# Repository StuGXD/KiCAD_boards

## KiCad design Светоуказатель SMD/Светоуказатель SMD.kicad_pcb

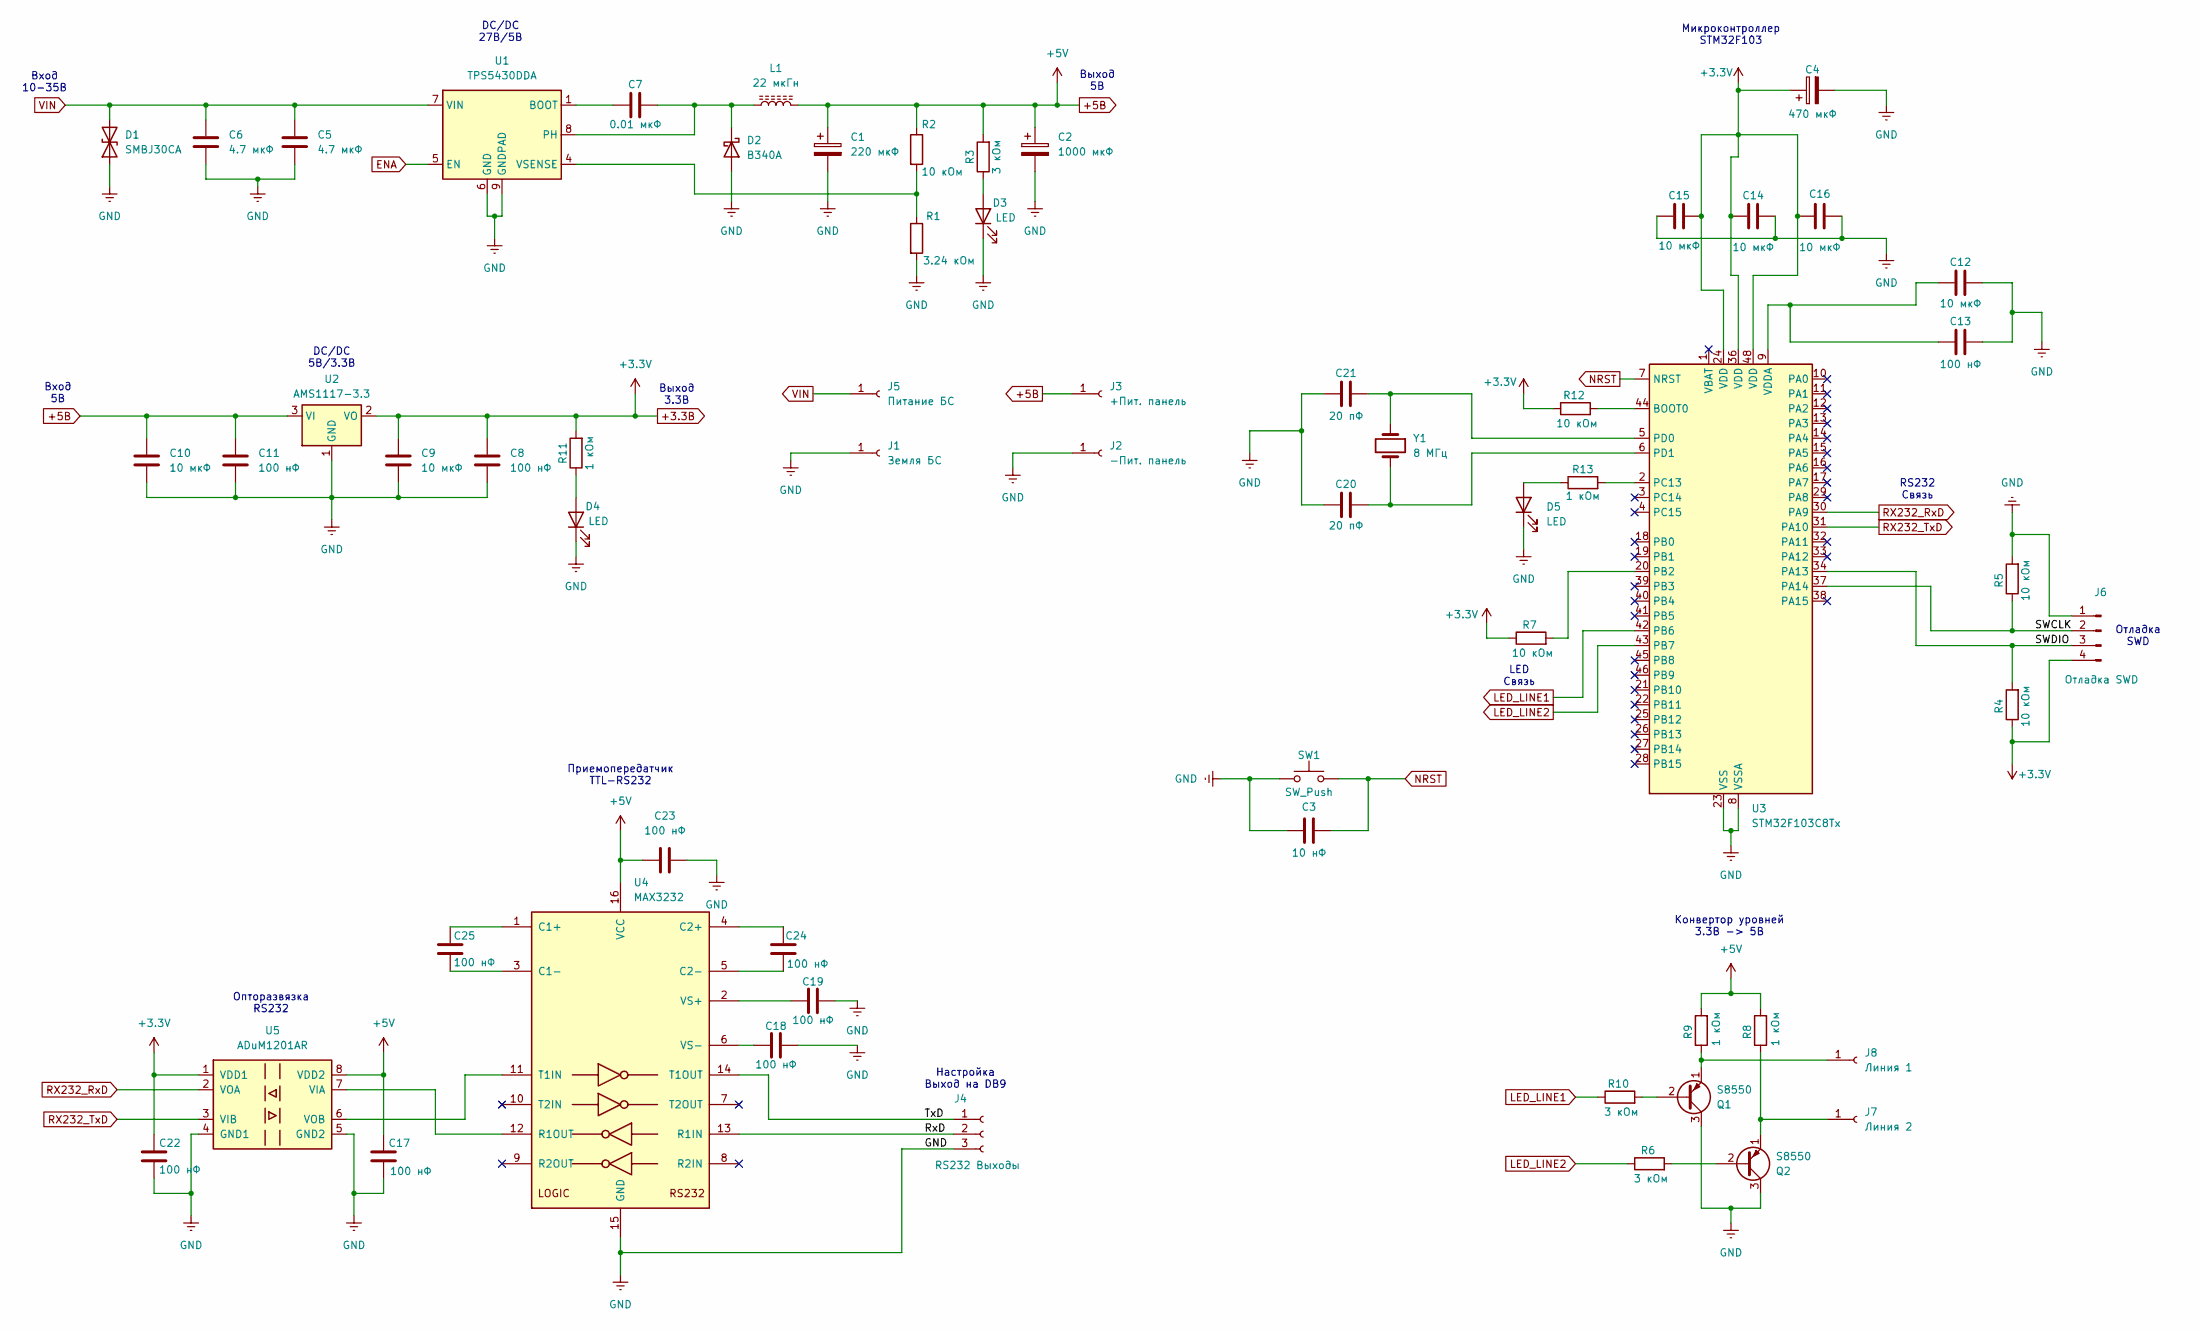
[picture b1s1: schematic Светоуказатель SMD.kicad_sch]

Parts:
C1: 220 мкФ; C_0603_1608Metric
C2: 1000 мкФ; CP_EIA-7343-43_Kemet-X_Pad2.25x2.55mm_HandSolder
C3: 10 нФ; C_0603_1608Metric
C4: 470 мкФ; CP_EIA-7343-43_Kemet-X_Pad2.25x2.55mm_HandSolder
C5, C6: 4.7 мкФ; C_0603_1608Metric
C7: 0.01 мкФ; C_0603_1608Metric
C8, C11, C13, C17, C18, C19, C22, C23, C24, C25: 100 нФ; C_0603_1608Metric
C9, C10, C12, C14, C15, C16: 10 мкФ; C_0603_1608Metric
C20, C21: 20 пФ; C_0603_1608Metric
D1: SMBJ30CA; D_SMB
D2: B340A; D_SMC
D3, D4, D5: LED; LED_0603_1608Metric
J1: Земля БС; SolderWire-2.5sqmm_1x01_D2.4mm_OD4.4mm
J2: -Пит. панель; SolderWire-2.5sqmm_1x01_D2.4mm_OD4.4mm
J3: +Пит. панель; SolderWire-2.5sqmm_1x01_D2.4mm_OD4.4mm
J4: RS232 Выходы; SolderWire-1sqmm_1x03_P7.8mm_D1.4mm_OD3.9mm
J5: Питание БС; SolderWire-2.5sqmm_1x01_D2.4mm_OD4.4mm
J6: Отладка SWD; PinHeader_1x04_P2.54mm_Vertical
J7: Линия 2; SolderWire-2.5sqmm_1x01_D2.4mm_OD4.4mm
J8: Линия 1; SolderWire-2.5sqmm_1x01_D2.4mm_OD4.4mm
L1: 22 мкГн; L_Bourns_SRR1260
Q1, Q2: S8550; SOT-23
R1: 3.24 кОм; R_0603_1608Metric
R2, R4, R5, R7, R12: 10 кОм; R_0603_1608Metric
R3, R6, R10: 3 кОм; R_0603_1608Metric
R8, R9, R11, R13: 1 кОм; R_0603_1608Metric
SW1: SW_Push; SW_SPST_CK_RS282G05A3
U1: TPS5430DDA; TI_SO-PowerPAD-8_ThermalVias
U2: AMS1117-3.3; SOT-223-3_TabPin2
U3: STM32F103C8Tx; LQFP-48_7x7mm_P0.5mm
U4: MAX3232; TSSOP-16_4.4x5mm_P0.65mm
U5: ADuM1201AR; SOIC-8_3.9x4.9mm_P1.27mm
Y1: 8 МГц; Crystal_SMD_HC49-SD

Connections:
+3.3В: C4.1, C8.1, C9.1, C14.2, C15.2, C16.1, C22.2, J6.4, R4.1, R7.1, R11.2, R12.1, U2.2 (VO), U3.24 (VDD), U3.36 (VDD), U3.48 (VDD), U5.1 (VDD1)
+5В: C1.1, C2.1, C10.1, C11.1, C17.1, C23.1, J3.1, L1.2, R2.1, R3.2, R8.2, R9.2, U2.3 (VI), U4.16 (VCC), U5.8 (VDD2)
/RxD: J4.2, U4.13 (R1IN)
/SWCLK: J6.2, R5.1, U3.37 (PA14)
/SWDIO: J6.3, R4.2, U3.34 (PA13)
/TxD: J4.1, U4.14 (T1OUT)
ENA: U1.5 (EN)
GND: C1.2, C2.2, C3.1, C4.2, C5.2, C6.2, C8.2, C9.2, C10.2, C11.2, C12.2, C13.2, C14.1, C15.1, C16.2, C17.2, C18.2, C19.2, C20.1, C21.1, C22.1, C23.2, D1.1 (A1), D2.2 (A), D3.1 (K), D4.1 (K), D5.1 (K), J1.1, J2.1, J4.3, J6.1, Q1.3 (C), Q2.3 (C), R1.2, R5.2, SW1.1, U1.6 (GND), U1.9 (GNDPAD), U2.1 (GND), U3.8 (VSSA), U3.23 (VSS), U3.35 (VSS), U3.47 (VSS), U4.15 (GND), U5.4 (GND1), U5.5 (GND2)
LED_LINE1: R10.1, U3.42 (PB6)
LED_LINE2: R6.1, U3.43 (PB7)
NRST: C3.2, SW1.2, U3.7 (NRST)
unnamed: C7.2, D2.1 (K), L1.1, U1.8 (PH)
unnamed: D3.2 (A), R3.1
unnamed: D4.2 (A), R11.1
unnamed: D5.2 (A), R13.1
unnamed: J7.1, Q2.1 (E), R8.1
unnamed: J8.1, Q1.1 (E), R9.1
unnamed: Q1.2 (B), R10.2
unnamed: Q2.2 (B), R6.2
unnamed: C7.1, U1.1 (BOOT)
unnamed: R1.1, R2.2, U1.4 (VSENSE)
unnamed: R12.2, U3.44 (BOOT0)
unnamed: R7.2, U3.20 (PB2)
unnamed: R13.2, U3.2 (PC13)
unnamed: C21.2, U3.5 (PD0), Y1.1
unnamed: C20.2, U3.6 (PD1), Y1.2
unnamed: C12.1, C13.1, U3.9 (VDDA)
unnamed: C25.1, U4.1 (C1+)
unnamed: C25.2, U4.3 (C1-)
unnamed: C24.1, U4.4 (C2+)
unnamed: C24.2, U4.5 (C2-)
unnamed: U4.12 (R1OUT), U5.7 (VIA)
unnamed: U4.11 (T1IN), U5.6 (VOB)
unnamed: C19.1, U4.2 (VS+)
unnamed: C18.1, U4.6 (VS-)
RX232_RxD: U3.30 (PA9), U5.2 (VOA)
RX232_TxD: U3.31 (PA10), U5.3 (VIB)
VIN: C5.1, C6.1, D1.2 (A2), J5.1, U1.7 (VIN)

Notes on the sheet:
Вход 5В
Отладка SWD
Вход 10-35В
Выход 5В
Микроконтроллер STM32F103
Опторазвязка RS232
Выход 3.3В
Конвертор уровней 3.3В -> 5В
DC/DC 5В/3.3В
DC/DC 27В/5В
LED Связь
Настройка Выход на DB9
RS232 Связь
Приемопередатчик TTL-RS232

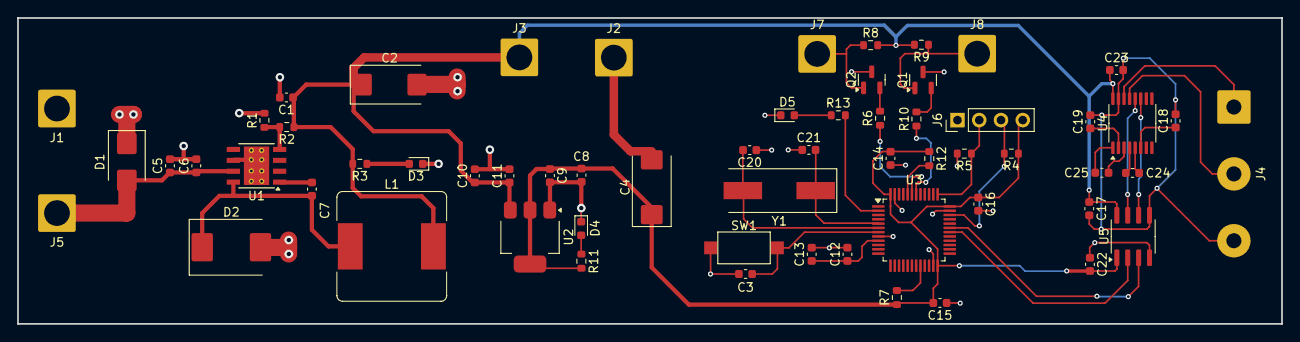
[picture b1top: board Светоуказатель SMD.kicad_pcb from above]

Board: 2 copper layers, 147.5 x 35.7 mm, 61 parts (0 on the bottom side), 37 nets.

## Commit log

2024-08-05 Led Control Board
    Project for led control via RS232 using GD32/STM32 F103 MCU.
2024-08-05 Add PCB file.
    Add pcb and components to project.
2024-08-06 Add some routing
    Add net routing for input power and DC/DC 3.3v.
2024-08-06 MCU net routing.
    Add MCU routing to project.
2024-08-06 Add full component places.
    Set component places for board without routing.
2024-08-07 Full routing add.
    Complete full touting for board.
2024-08-08 Final Design for Board.
    All design done.
2024-08-08 Cap moved.
    Move cap from electro to tantal.
